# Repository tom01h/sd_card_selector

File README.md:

# ラズパイ5のマイクロSDカードをリモートで書き換えたり、リモートで電源ONにできるやつ

## できること
- マイクロSDカードの接続をラズパイとUSBカードリーダーで切り替えられる
    - 接続の切り替え部分は[これ](https://x.com/task_jp/status/1864548270422573205)の真似
- 電源ボタンを押したのと同じことができる
    - [この資料](https://www.raspberrypi.com/documentation/computers/raspberry-pi.html#add-your-own-power-button)の通りに制御する
- 電源の状態を知れる
    - マイクロSDに供給されている電源を監視
- PCとUSB-UART的なもの（正確にはUSB CDC ACM）で繋ぐ
    - CH552マイコンを使って制御している

## 使い方
こんな感じに組み立てます  
USB-UARTもあったほうが便利です  

ラズパイの電源を入れる前にUSBハブをPCに繋ぎます  
ターミナルの表示は以下  
この状態ではPCからuSDカードにアクセスできます  
```
Raspberry Pi Remote
USB Card Reader
USB> 
```

`rpi`を入力してuSDの接続をラズパイに切り替えます  
この状態ではPCからuSDカードにアクセスできません  
```
USB> rpi
Raspberry Pi
Pi Off>
```

ラスパイの電源を入れて、ターミナルでエンターを入力すると下のような表示になります  
```
Pi Off>
Undefined Command
Pi On>
```

ラスパイをシャットダウンして、ターミナルでエンターを入力すると下のような表示になります  
```
Pi On>
Undefined Command
Pi Off>
```

`pon`を入力してラズパイの電源をONにします  
ターミナルでエンターを入力すると下のような表示になります  
```
Pi Off> pon
Power ON
Pi Off>
Undefined Command
Pi On>
```

`Pi Off`の状態から`usb`コマンドを入力すると、PCからuSDカードにアクセス出来るようになります  
```
Pi Off> usb
USB Card Reader
USB>
```

`Pi On`状態で`shutdown`コマンド実行で、強制的にラズパイの電源をOFFにできます（OSのシャットダウンではありません）  
その後、PCからuSDカードにアクセス出来るようになります  

## 部品
- [USBハブ](https://ja.aliexpress.com/item/1005007046850790.html?spm=a2g0o.order_list.order_list_main.20.7e81585a35DO0V&gatewayAdapt=glo2jpn)
- [USBカードリーダー](https://ja.aliexpress.com/item/1005007634731826.html?spm=a2g0o.order_list.order_list_main.30.7e81585a35DO0V&gatewayAdapt=glo2jpn)
- [USBエクステンションアダプター](https://ja.aliexpress.com/item/1005007404846946.html?spm=a2g0o.order_list.order_list_main.35.7e81585a35DO0V&gatewayAdapt=glo2jpn)
    - コの字型でUSB3.0のやつ
- 自作の基板
    - 設計データはKiCadディレクトリ以下
    - 基板の厚さは0.8mm

### 基板に乗せる部品
- [CH552](https://ja.aliexpress.com/item/1005004508033849.html?spm=a2g0o.order_list.order_list_main.5.138b585aBJw2jm&gatewayAdapt=glo2jpn)
    - CH552T
- [tmux1574pwr](https://ja.aliexpress.com/item/1005007848132137.html?spm=a2g0o.order_list.order_list_main.15.138b585aBJw2jm&gatewayAdapt=glo2jpn)
- [1N5819 SOD-123](https://ja.aliexpress.com/item/1005003194674618.html?spm=a2g0o.order_list.order_list_main.20.138b585aBJw2jm&gatewayAdapt=glo2jpn)
- [XC6206P332MR](https://ja.aliexpress.com/item/1005002918096822.html?spm=a2g0o.order_list.order_list_main.5.5ee2585acfyiWX&gatewayAdapt=glo2jpn)
- [ボタン](https://ja.aliexpress.com/item/32756768334.html?spm=a2g0o.productlist.main.13.1a30k3VJk3VJE4&algo_pvid=fc0dd005-b246-4df2-92c3-029a18e87beb&algo_exp_id=fc0dd005-b246-4df2-92c3-029a18e87beb-6&pdp_npi=4%40dis%21JPY%2184%2184%21%21%210.53%210.53%21%402101590d17375500547186651ede79%2164666626003%21sea%21JP%212693366707%21X&curPageLogUid=l37UiVKB93k7&utparam-url=scene%3Asearch%7Cquery_from%3A)
    - 買ったやつはリンクなくなった・多分これと同じ
- 抵抗とか容量は1206サイズ（3.2mmx1.6mm）

## 基板の繋ぎ方
### 作成した基板の実装
こんな感じ  

uSDカードスロットのフットプリントはギリギリ使えるくらいにずれています

### SDカードリーダーの改造
カードリーダーの基板を取り出します  

uSDスロットのカードデテクトを壊します  
カードを入れてもdetectピンがグランドに落ちないようにします  

カードリーダーのSDスロットを外します  
外したソケットのパターンのデテクトピンと作成した基板のTP1を繋ぎます  

### USBハブの接続
コの字型のアダプタも使ってこんな感じにつなぐ  
5㎜厚の両面テープを3段重ねで止めています  

### ピンヘッダ(J2)の接続
- 1PINはPSWピンヘッダの1PIN
- 2PINはPSWピンヘッダの2PIN (GND)
- 3PINはラズパイピンヘッダの5V出力
    - 電源はUSBからもとっているので、この接続がなくても動きます

## CH552のソフト
[ch55xduino](https://github.com/DeqingSun/ch55xduino)を使って、CH552にArduino IDEからプログラム(Arduino/SDSEL/SDSEL.ino)を書きみます  
プログラムの書き込みには[WCHISPTool](https://www.wch.cn/downloads/WCHISPTool_Setup_exe.html)が必要です

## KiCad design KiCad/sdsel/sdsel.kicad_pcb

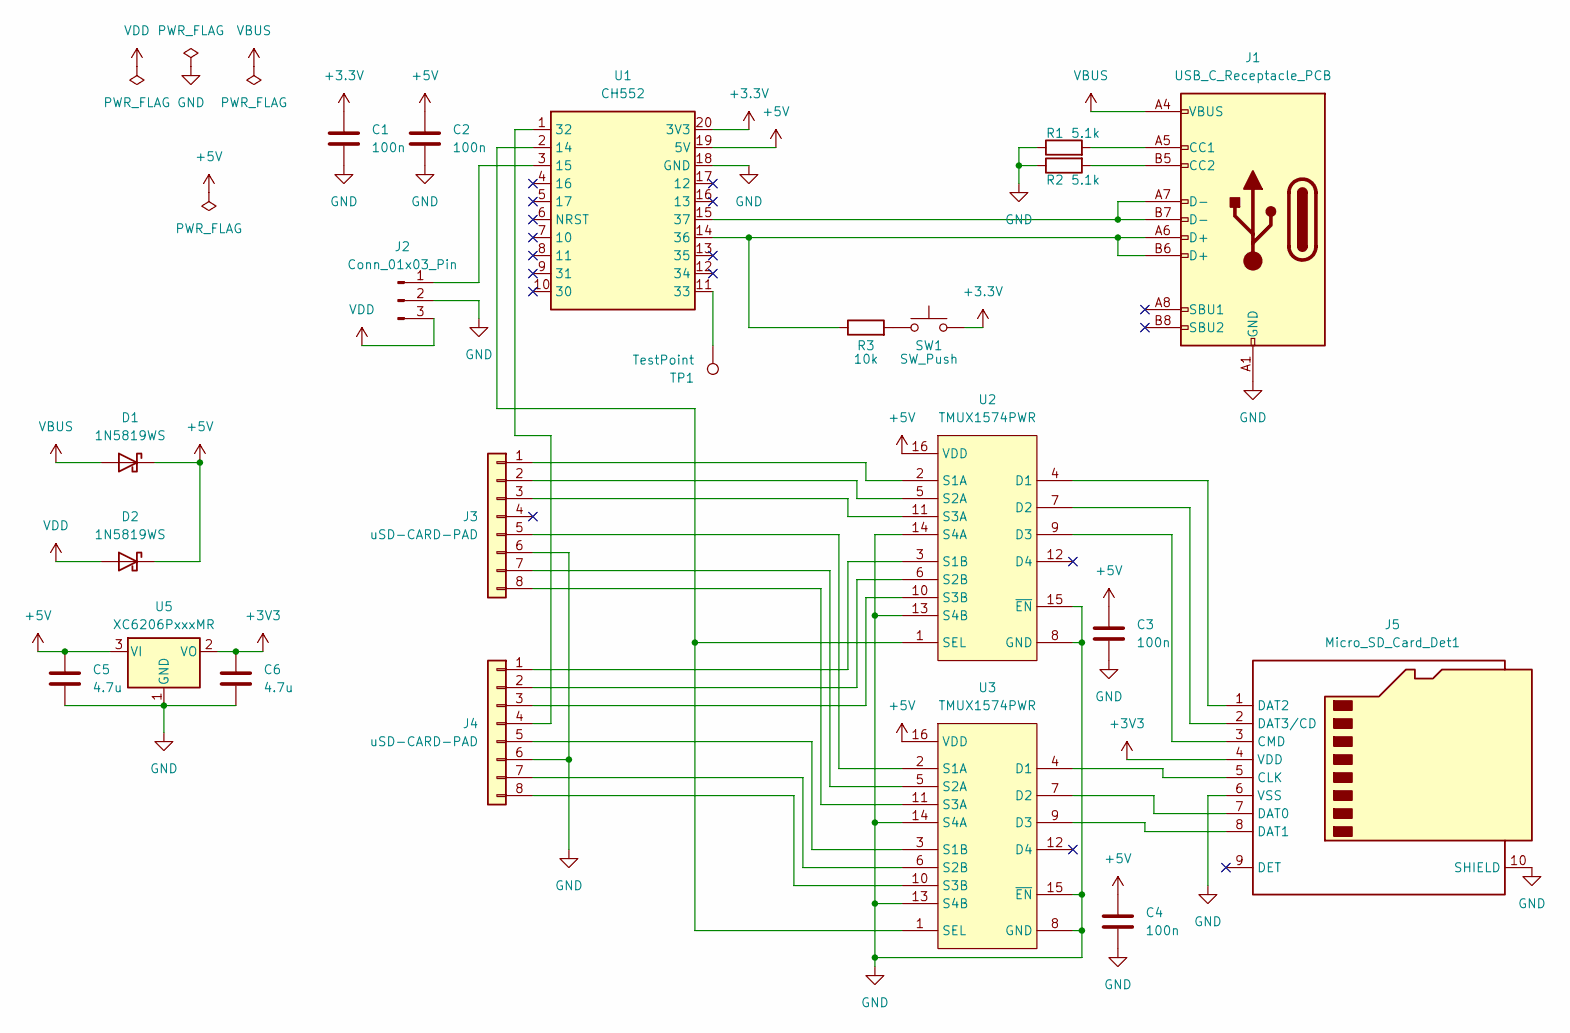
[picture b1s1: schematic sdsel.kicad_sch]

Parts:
C1, C2, C3, C4: 100n; C_1206_3216Metric_Pad1.33x1.80mm_HandSolder
C5, C6: 4.7u; C_1206_3216Metric_Pad1.33x1.80mm_HandSolder
D1, D2: 1N5819WS; Nexperia_CFP3_SOD-123W
J1: USB_C_Receptacle_PCB
J2: Conn_01x03_Pin; PinHeader_1x03_P2.54mm_Vertical
J3, J4: uSD-CARD-PAD; uSD-PAD
J5: Micro_SD_Card_Det1; microsd
R1, R2: 5.1k; R_1206_3216Metric_Pad1.30x1.75mm_HandSolder
R3: 10k; R_1206_3216Metric_Pad1.30x1.75mm_HandSolder
SW1: SW_Push; SW_SPST_CK_RS282G05A3
TP1: TestPoint; TestPoint_Pad_1.0x1.0mm
U1: CH552; TSSOP-20_4.4x6.5mm_P0.65mm
U2, U3: TMUX1574PWR; TSSOP-16_4.4x5mm_P0.65mm
U5: XC6206PxxxMR; SOT-23-3

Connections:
+3.3V: C1.1, SW1.2, U1.20 (3V3)
+3V3: C6.1, J5.4 (VDD), U5.2 (VO)
+5V: C2.1, C3.1, C4.1, C5.1, D1.1 (K), D2.1 (K), U1.19 (5V), U2.16 (VDD), U3.16 (VDD), U5.3 (VI)
GND: C1.2, C2.2, C3.2, C4.2, C5.2, C6.2, J1.A1 (GND), J1.A12 (GND), J1.B1 (GND), J1.B12 (GND), J2.2, J3.6, J4.6, J5.6 (VSS), J5.10 (SHIELD), R1.1, R2.1, U1.18 (GND), U2.8 (GND), U2.13 (S4B), U2.14 (S4A), U2.15 (~EN), U3.8 (GND), U3.13 (S4B), U3.14 (S4A), U3.15 (~EN), U5.1 (GND)
unnamed: J1.A5 (CC1), R1.2
unnamed: J1.B5 (CC2), R2.2
unnamed: J2.1, U1.3 (15)
unnamed: J3.1, U2.2 (S1A)
unnamed: J3.2, U2.5 (S2A)
unnamed: J3.3, U2.11 (S3A)
unnamed: J3.5, U3.2 (S1A)
unnamed: J3.7, U3.5 (S2A)
unnamed: J3.8, U3.11 (S3A)
unnamed: J4.1, U2.3 (S1B)
unnamed: J4.2, U2.6 (S2B)
unnamed: J4.3, U2.10 (S3B)
unnamed: J4.4, U1.1 (32)
unnamed: J4.5, U3.3 (S1B)
unnamed: J4.7, U3.6 (S2B)
unnamed: J4.8, U3.10 (S3B)
unnamed: J5.5 (CLK), U3.4 (D1)
unnamed: J5.3 (CMD), U2.9 (D3)
unnamed: J5.7 (DAT0), U3.7 (D2)
unnamed: J5.8 (DAT1), U3.9 (D3)
unnamed: J5.1 (DAT2), U2.4 (D1)
unnamed: J5.2 (DAT3/CD), U2.7 (D2)
unnamed: R3.2, SW1.1
unnamed: U1.2 (14), U2.1 (SEL), U3.1 (SEL)
unnamed: TP1.1, U1.11 (33)
unnamed: J1.A6 (D+), J1.B6 (D+), R3.1, U1.14 (36)
unnamed: J1.A7 (D-), J1.B7 (D-), U1.15 (37)
VBUS: D1.2 (A), J1.A4 (VBUS), J1.A9 (VBUS), J1.B4 (VBUS), J1.B9 (VBUS)
VDD: D2.2 (A), J2.3

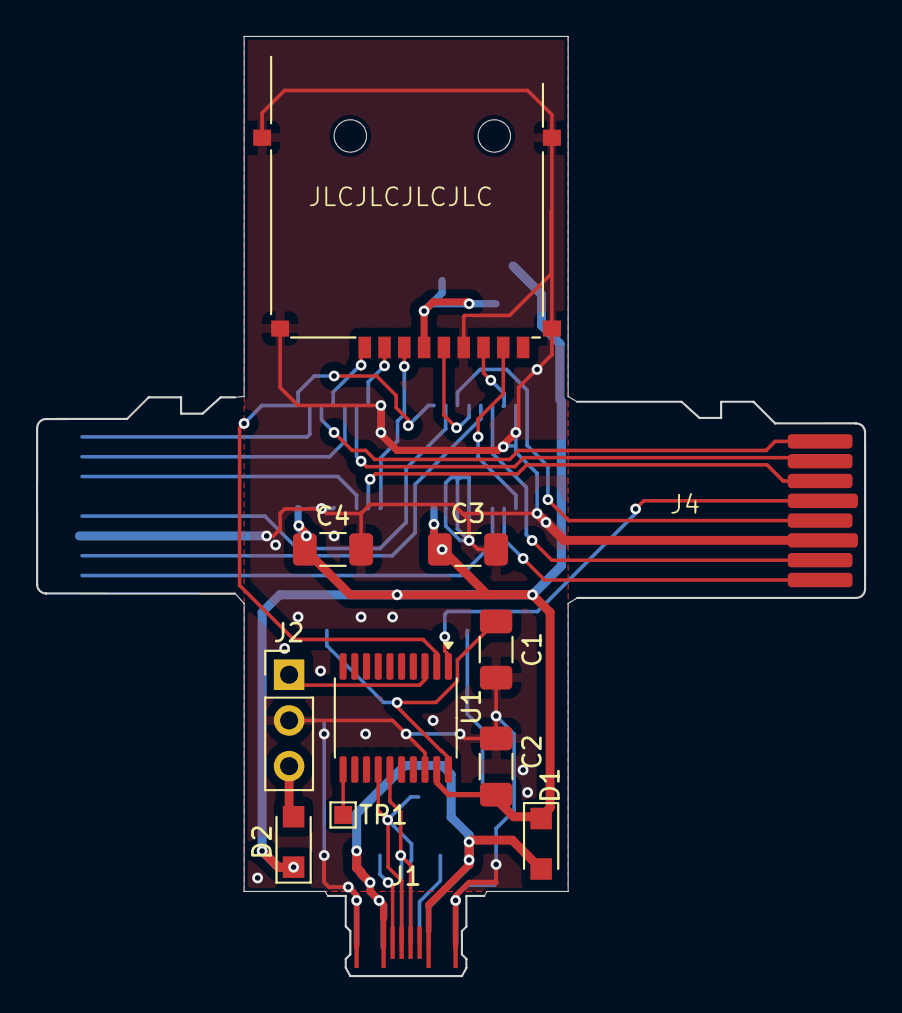
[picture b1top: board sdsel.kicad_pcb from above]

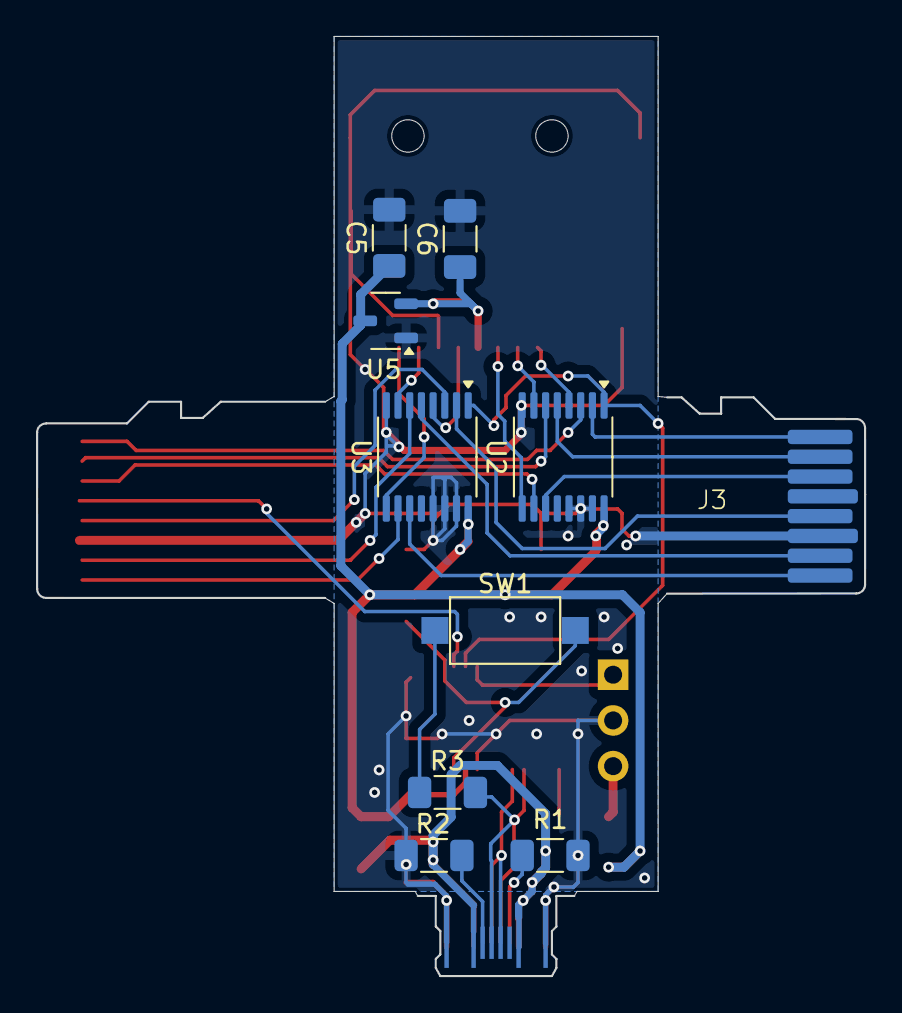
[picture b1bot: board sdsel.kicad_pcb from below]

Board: 2 copper layers, 46.0 x 52.2 mm, 22 parts (10 on the bottom side), 33 nets.

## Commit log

2025-01-22 initial
2025-01-22 README
2025-01-23 基板の繋ぎ方
2025-02-13 README
    カードデテクトの破壊方法変更
